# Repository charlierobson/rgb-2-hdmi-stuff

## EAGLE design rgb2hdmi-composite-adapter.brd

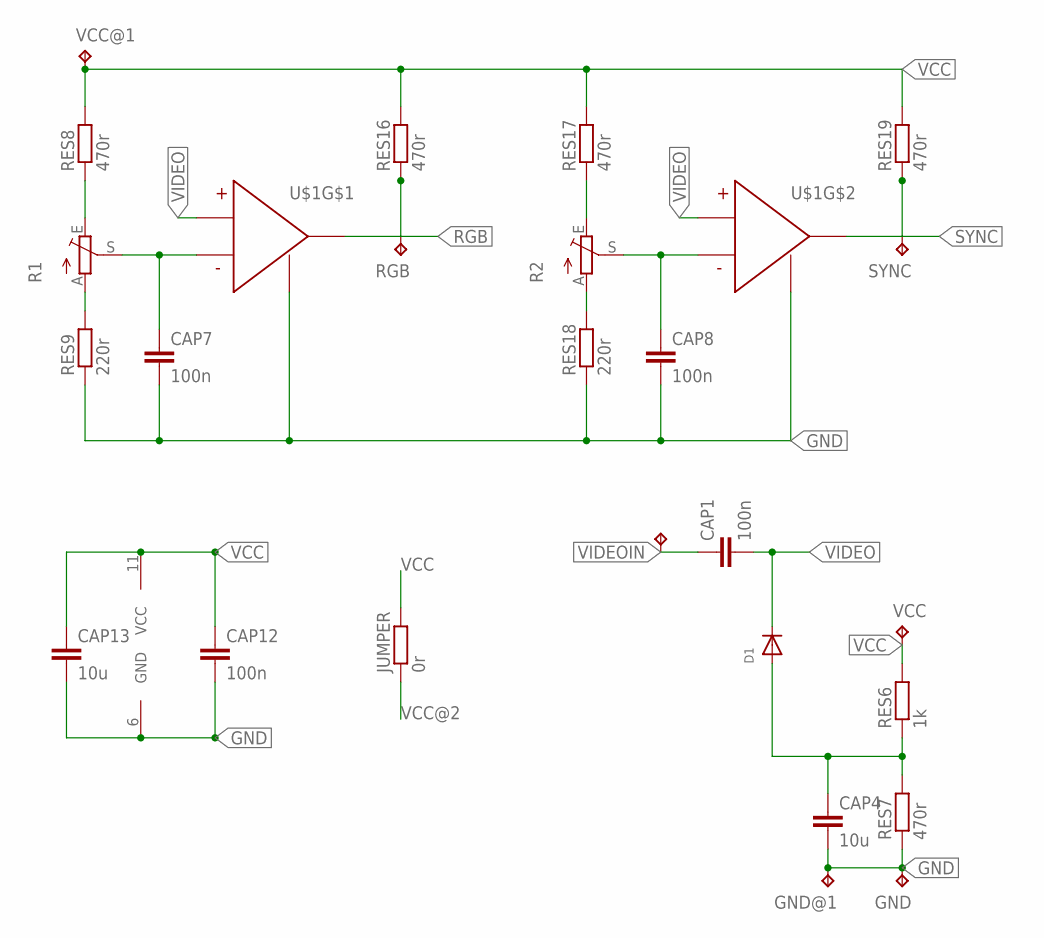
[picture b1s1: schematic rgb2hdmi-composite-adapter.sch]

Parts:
CAP1, CAP7, CAP8, CAP12: 100n; C025-025X050
CAP4, CAP13: 10u; C025-025X050
D1: DIODEDO-1N4148; DO-1N4148
GND: TPPAD1-17Y; P1-17Y
GND@1: TPPAD1-17Y; P1-17Y
JUMPER: 0r; 0207/10
R1, R2: TRIM_EU-B64Y; B64Y
RES6: 1k; 0207/10
RES7, RES8, RES16, RES17, RES19: 470r; 0207/10
RES9, RES18: 220r; 0207/10
RGB: TPPAD1-17Y; P1-17Y
SYNC: TPPAD1-17Y; P1-17Y
U$1: LM319PROPER-DIL-14; DIL14
VCC: TPPAD1-17Y; P1-17Y
VCC@1: TPPAD1-17Y; P1-17Y
VIDEOIN: TPPAD1-17Y; P1-17Y

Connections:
GND: CAP4.2, CAP7.2, CAP8.2, CAP12.2, CAP13.2, GND.TP, GND@1.TP, RES7.1, RES9.1, RES18.1, U$1.3 (GND), U$1.6 (GND), U$1.8 (GND)
unnamed: CAP4.1, D1.A, RES6.1, RES7.2
unnamed: R1.A, RES9.2
unnamed: R2.E, RES17.1
unnamed: R2.A, RES18.2
unnamed: R1.E, RES8.1
RGB: RES16.1, RGB.TP, U$1.12 (OUT)
RGBTRIM: CAP7.1, R1.S, U$1.5 (INV)
SYNC: RES19.1, SYNC.TP, U$1.7 (OUT)
SYNCTRIM: CAP8.1, R2.S, U$1.10 (INV)
VCC: CAP12.1, CAP13.1, JUMPER.2, RES6.2, RES8.2, RES16.2, RES17.2, RES19.2, U$1.11 (VCC), VCC.TP, VCC@1.TP
VCC@2: JUMPER.1
VIDEO: CAP1.2, D1.C, U$1.4 (NONINV), U$1.9 (NONINV)
VIDEOIN: CAP1.1, VIDEOIN.TP

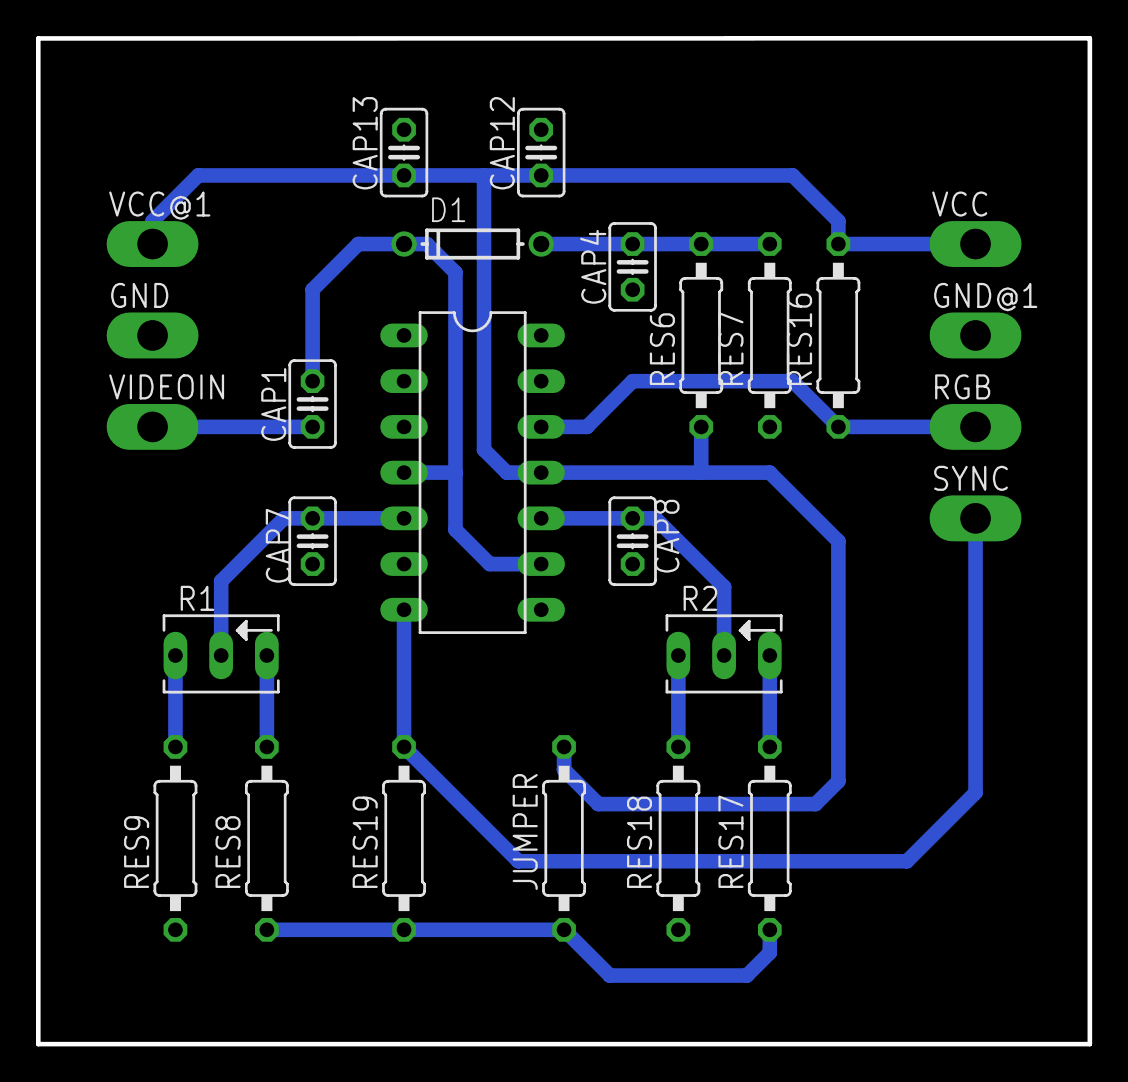
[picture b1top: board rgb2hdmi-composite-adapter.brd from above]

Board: 2 copper layers, 58.4 x 55.9 mm, 26 parts (0 on the bottom side), 13 nets.

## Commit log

2019-04-25 update design
2019-04-26 latest, w/new 319
2019-04-26 add scope images
2019-04-26 update for wiki
2019-04-26 add original schema
2019-04-26 fix image
